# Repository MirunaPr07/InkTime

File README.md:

# InkWatch_TSC_Project

## Descriere

Proiectul meu este un smartwatch simplificat, cu focus pe consum redus și integrarea mai multor funcționalități pe un PCB mic. Am folosit un nRF52840 ca MCU principal și am conectat la el senzori, display e-paper și haptic.

Funcționalități:
- display e-paper
- BLE pentru comunicare
- accelerometru pentru mișcare
- feedback haptic
- încărcare USB-C

---

## Schema Bloc

```mermaid
graph TD

    USB["USB-C (J4)"] --> CHARGER["BQ25180 Charger"]
    CHARGER --> REG["RT6160 3.3V"]
    REG --> MCU["nRF52840 MCU + BLE"]

    BAT["LiPo Battery"] --> CHARGER
    BAT --> FUEL["MAX17048 Fuel Gauge"]
    FUEL --> MCU

    MCU -->|SPI| EPD["EPD Display (J1)"]
    MCU -->|I2C| IMU["BMA421 IMU"]
    MCU -->|I2C| HAPTIC["DRV2605 Haptic"]

    MCU --> BTN1["SW_UP"]
    MCU --> BTN2["SW_DN"]
    MCU --> BTN3["SW_ENT"]

    MCU --> ANT["2.4GHz Antenna"]

    MCU --> DEBUG["TC2030 SWD"]
```

## Bill of Materials

| Ref | Component | Package | Funcție | LCSC | Datasheet |
|-----|----------|--------|--------|------|----------|
| U1 | nRF52840-QIAA | QFN73 | MCU + BLE | [C190794](https://jlcpcb.com/partdetail/C190794) | https://infocenter.nordicsemi.com |
| IC1 | BQ25180YBGR | DSBGA-8 | Charger LiPo | [C3682423](https://jlcpcb.com/partdetail/C3682423) | https://www.ti.com |
| IC9 | RT6160AWSC | WLCSP-15 | Regulator 3.3V | [C7065276](https://jlcpcb.com/partdetail/C7065276) | https://www.richtek.com |
| U3 | MAX17048G+T10 | DFN | Fuel gauge | [C2682616](https://jlcpcb.com/partdetail/C2682616) | https://www.analog.com |
| IC3 | BMA421 | LGA | IMU | [C5242966](https://jlcpcb.com/partdetail/C5242966) | https://www.bosch-sensortec.com |
| IC2 | DRV2605L | VSSOP | Haptic driver | [C527464](https://jlcpcb.com/partdetail/C527464) | https://www.ti.com |
| D3 | USBLC6 | SOT-23-6 | ESD USB | [C2687116](https://jlcpcb.com/partdetail/C2687116) | https://www.st.com |
| J4 | USB-C | SMD | Conector alimentare | [C165948](https://jlcpcb.com/partdetail/C165948) | - |
| J1 | FPC 24 pini | SMD | Conector display | [C393234](https://jlcpcb.com/partdetail/C393234) | - |
| J2 | TC2030 | PTH | Debug SWD | - | - |
| ANT1 | 2450AT18B100E | SMD | Antenă BLE | - | https://www.johansontechnology.com |

---

## Funcționalitate Hardware

### Power

USB-C (5V) -> BQ25180 -> RT6160 -> 3.3V -> sistem

- BQ25180 face charging + power path
- RT6160 generează 3.3V stabil
- MAX17048 citește nivelul bateriei

---

### MCU - nRF52840

Este componenta principală:
- BLE integrat
- controlează toate perifericele

---

### Display E-Paper

Conectat prin SPI:
- SCK - P0.02
- MOSI - P0.03
- CS - P0.05
- DC - P0.15
- RST - P0.16
- BUSY - P0.17

---

### IMU - BMA421

- I2C (SDA P0.06 / SCL P0.07)
- interrupt pe P0.08 și P1.08

---

### Haptic – DRV2605

- I2C
- enable pe P0.12

---

### USB

- USB-C pentru alimentare
- protecție ESD (USBLC6)

---

## Pini nRF52840

| Pin | Semnal | Funcție |
|-----|--------|--------|
| P0.02 | SCK | SPI |
| P0.03 | MOSI | SPI |
| P0.05 | CS | Display |
| P0.06 | SDA | I2C |
| P0.07 | SCL | I2C |
| P0.08 | INT1 | IMU |
| P0.12 | HAPTIC_EN | Haptic |
| P0.13 | SW_UP | Buton |
| P0.14 | SW_DN | Buton |
| P0.15 | DC | Display |
| P0.16 | RST | Display |
| P0.17 | BUSY | Display |
| P1.00 | SW_ENT | Buton |
| P1.01 | EPD_PWR | Power gate |
| P1.08 | INT2 | IMU |
| P0.24 | SWDCLK | Debug |
| P0.25 | SWDIO | Debug |

---

## PCB Design

- 2 layere (Top + Bottom)
- GND polygon pour pe ambele
- trasee:
  - power: 0.3mm
  - semnal: 0.15mm

### Decizii:
- antena la margine cu keepout
- decuplare lângă IC-uri
- rutare manuală pentru trasee critice

---

## Observații

- rutare destul de densă în zona MCU
- unele trasee mai subțiri în zona BGA
- câteva GND trase manual

---

## Concluzie

Proiectul este complet funcțional din punct de vedere hardware și include toate modulele necesare pentru un smartwatch simplu.

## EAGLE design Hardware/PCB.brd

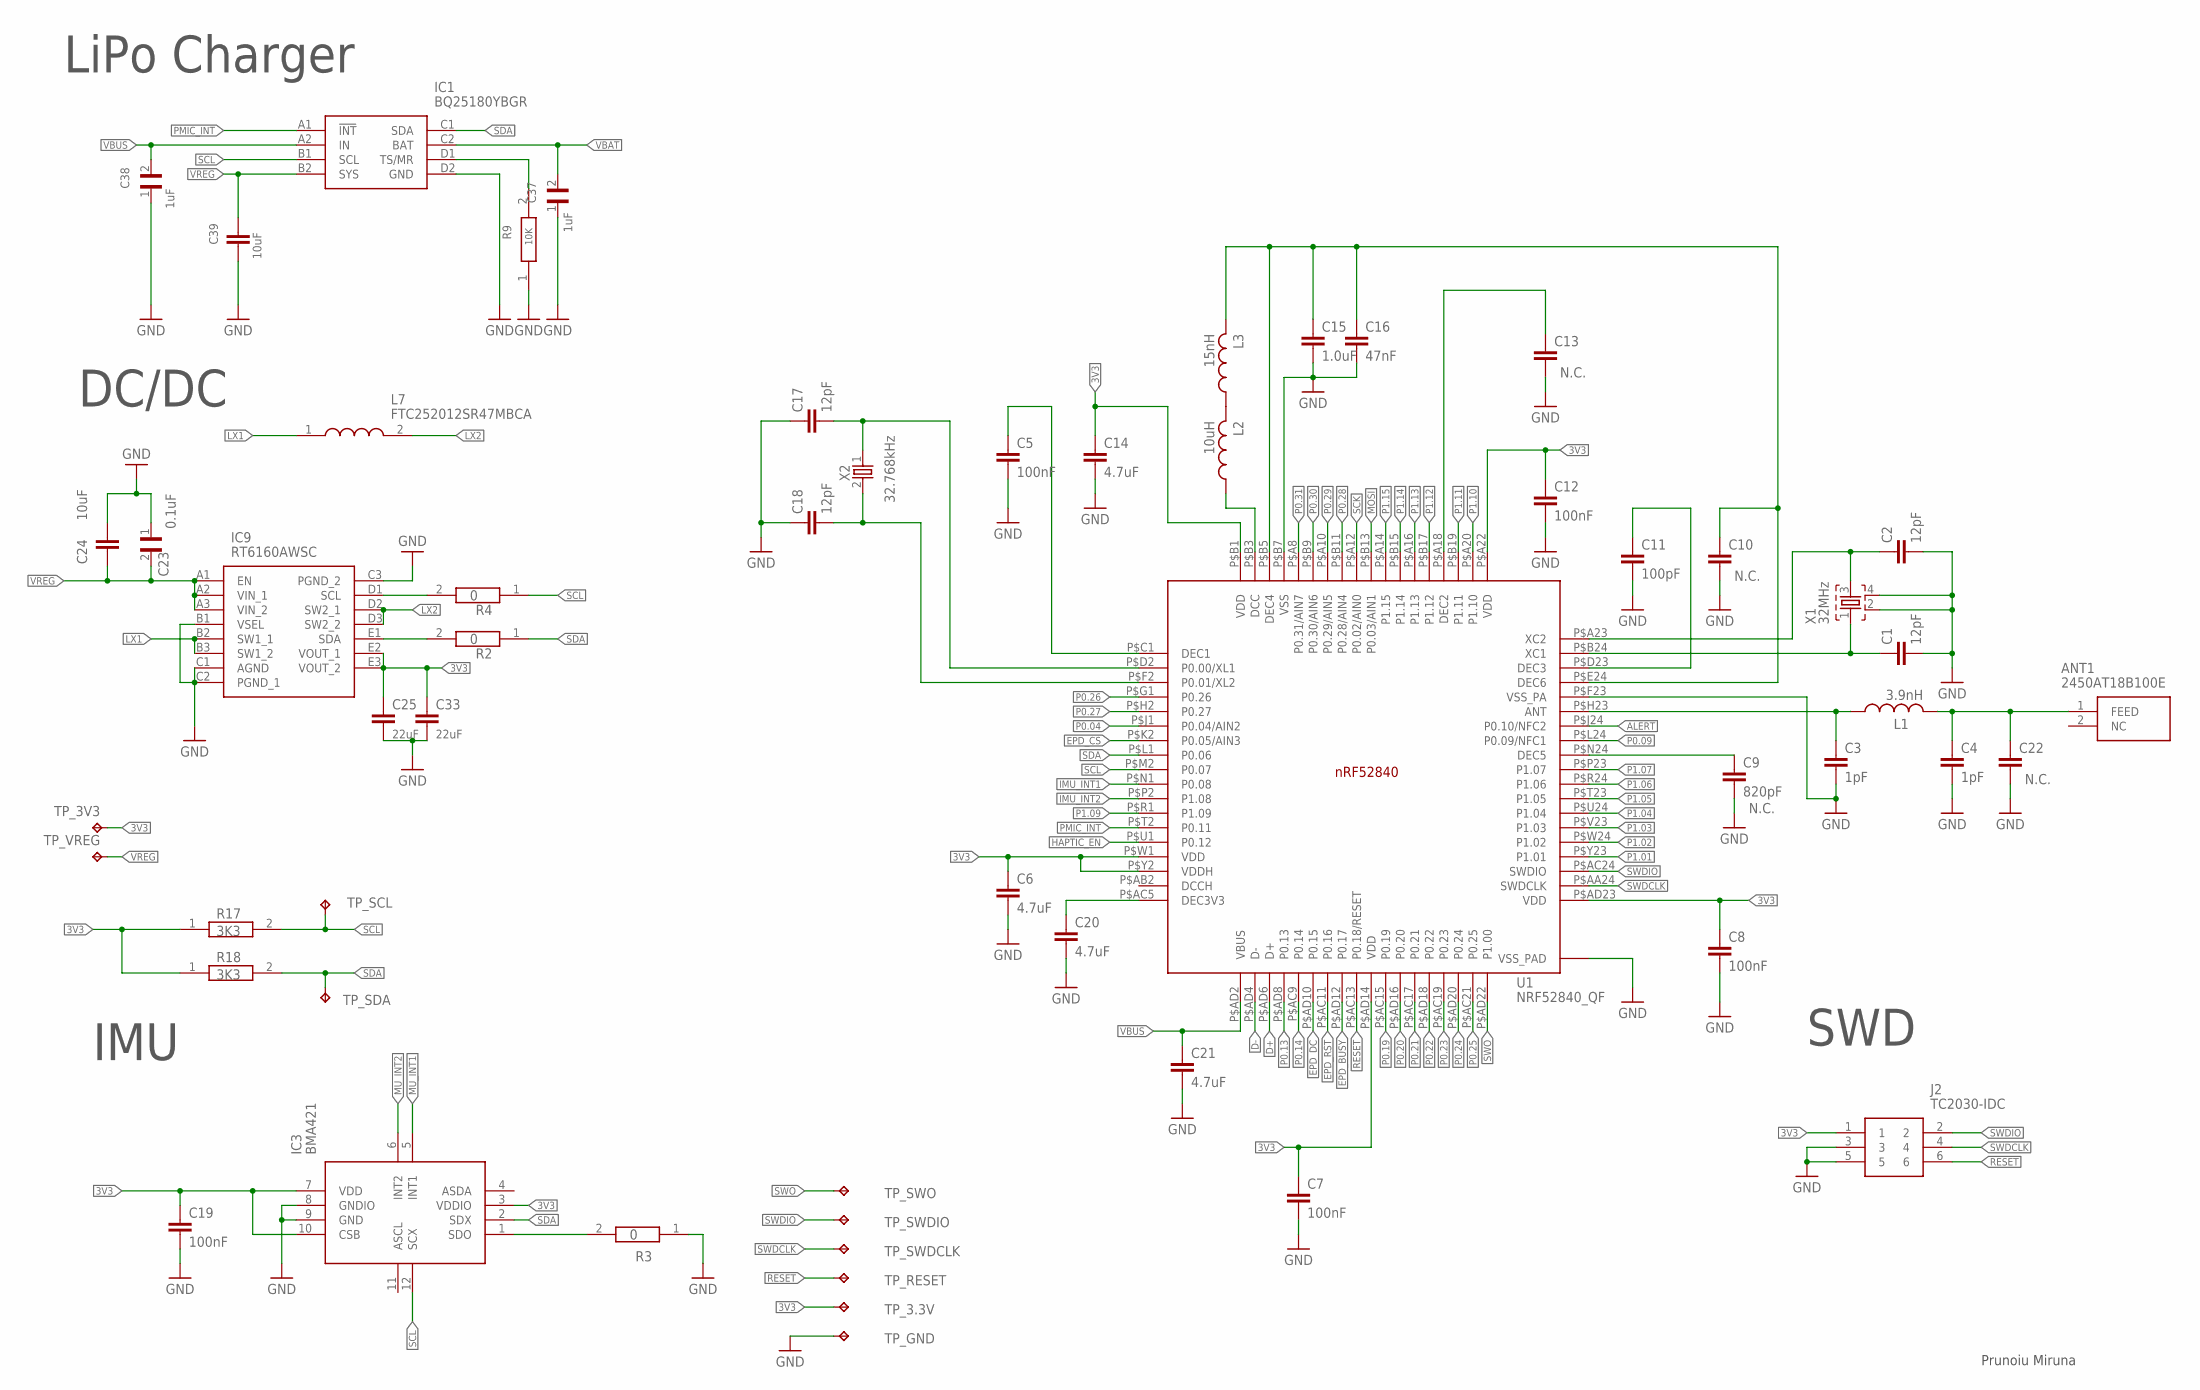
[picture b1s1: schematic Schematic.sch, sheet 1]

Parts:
ANT1: 2450AT18B100E; 2450AT18B100E_ANTC3216X140N
C1, C2, C17, C18: 12pF; NORDIC_NRF_3_RESC0201_L
C3, C4: 1pF; NORDIC_NRF_3_RESC0201_L
C5, C7, C8, C12, C19: 100nF; NORDIC_NRF_3_RESC0201_L
C6, C14, C20, C21: 4.7uF; NORDIC_NRF_3_RESC0201_L
C9: 820pF; NORDIC_NRF_3_RESC0201_L
C10, C13, C22: NORDIC_NRF_3_CAPACITOR_0201_L; NORDIC_NRF_3_RESC0201_L
C11: 100pF; NORDIC_NRF_3_RESC0201_L
C15: 1.0uF; NORDIC_NRF_3_RESC0201_L
C16: 47nF; NORDIC_NRF_3_RESC0201_L
C23: 0.1uF; GRM011R60J152KE01L_1_0201
C24, C39: 10uF; NORDIC_NRF_3_RESC0201_L
C25, C33: 22uF; NORDIC_NRF_3_RESC0201_L
C37, C38: 1uF; GRM011R60J152KE01L_1_0201
IC1: BQ25180YBGR; BQ25180YBGR_BGA8C40P2X4_100X155X50
IC3: BMA421; BMA423_BMA423
IC9: RT6160AWSC; RT6160AWSC_BGA15C40P3X5_140X230X60
J2: TC2030-IDC; TC2030-IDC_TC2030IDC
L1: 3.9nH; NORDIC_NRF_2_RESC0402_L
L2: 10uH; NORDIC_NRF_2_RESC0402_L
L3: 15nH; NORDIC_NRF_2_RESC0402_L
L7: FTC252012SR47MBCA; MLP2016SR47MT0S1_INDC2016X100N
R2, R3, R4: 0; CPF0201D7K68C1_0201
R9: 10K; CPF0201D7K68C1_0201
R17, R18: 3K3; CPF0201D7K68C1_0201
TP_3.3V, TP_3V3: HECTOR_WATCH_1_TPTP20R; HECTOR_WATCH_1_TP20R
TP_GND: HECTOR_WATCH_1_TPTP20R; HECTOR_WATCH_1_TP20R
TP_RESET: HECTOR_WATCH_1_TPTP20R; HECTOR_WATCH_1_TP20R
TP_SCL: HECTOR_WATCH_1_TPTP20R; HECTOR_WATCH_1_TP20R
TP_SDA: HECTOR_WATCH_1_TPTP20R; HECTOR_WATCH_1_TP20R
TP_SWDCLK: HECTOR_WATCH_1_TPTP20R; HECTOR_WATCH_1_TP20R
TP_SWDIO: HECTOR_WATCH_1_TPTP20R; HECTOR_WATCH_1_TP20R
TP_SWO: HECTOR_WATCH_1_TPTP20R; HECTOR_WATCH_1_TP20R
TP_VREG: HECTOR_WATCH_1_TPTP20R; HECTOR_WATCH_1_TP20R
U1: NRF52840_QF; NORDIC_NRF_4_AQFN50P700X700X85_HS-74N
X1: 32MHz; NORDIC_NRF_BT-XTAL_2016_N
X2: 32.768kHz; NORDIC_NRF_1_XTAL_3215_N

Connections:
3V3: C6.1, C7.1, C8.1, C12.1, C14.1, C19.1, C25.1, C33.1, IC3.3 (VDDIO), IC3.7 (VDD), IC3.10 (CSB), IC9.E2 (VOUT_1), IC9.E3 (VOUT_2), J2.1, R17.1, R18.1, TP_3.3V.TP, TP_3V3.TP, U1.P$A22 (VDD), U1.P$AD14 (VDD), U1.P$AD23 (VDD), U1.P$B1 (VDD), U1.P$W1 (VDD), U1.P$Y2 (VDDH); also elsewhere on the board
ALERT: U1.P$J24 (P0.10/NFC2); also elsewhere on the board
D+: U1.P$AD6 (D+); also elsewhere on the board
D-: U1.P$AD4 (D-); also elsewhere on the board
DEC1: C5.1, U1.P$C1 (DEC1)
DEC3: C11.1, U1.P$D23 (DEC3)
DEC4_6: C10.1, C15.1, C16.1, L3.2, U1.P$B5 (DEC4), U1.P$E24 (DEC6)
EPD_BUSY: U1.P$AD12 (P0.17); also elsewhere on the board
EPD_CS: U1.P$K2 (P0.05/AIN3); also elsewhere on the board
EPD_DC: U1.P$AD10 (P0.15); also elsewhere on the board
EPD_RST: U1.P$AC11 (P0.16); also elsewhere on the board
GND: C1.2, C2.2, C3.2, C4.2, C5.2, C6.2, C7.2, C8.2, C9.2, C10.2, C11.2, C12.2, C13.2, C14.2, C15.2, C16.2, C17.1, C18.1, C19.2, C20.2, C21.2, C22.2, C23.1, C24.1, C25.2, C33.2, C37.1, C38.1, C39.2, IC1.D2 (GND), IC3.8 (GNDIO), IC3.9 (GND), IC9.B1 (VSEL), IC9.C1 (AGND), IC9.C2 (PGND_1), IC9.C3 (PGND_2), J2.3, J2.5, R3.1, R9.1, TP_GND.TP, U1.P$74 (VSS_PAD), U1.P$75 (VSS_PAD), U1.P$76 (VSS_PAD), U1.P$77 (VSS_PAD), U1.P$78 (VSS_PAD), U1.P$79 (VSS_PAD), U1.P$80 (VSS_PAD), U1.P$81 (VSS_PAD), U1.P$82 (VSS_PAD), U1.P$83 (VSS_PAD), U1.P$84 (VSS_PAD), U1.P$85 (VSS_PAD), U1.P$86 (VSS_PAD), U1.P$87 (VSS_PAD), U1.P$88 (VSS_PAD), U1.P$89 (VSS_PAD), U1.P$90 (VSS_PAD), U1.P$B7 (VSS), U1.P$F23 (VSS_PA), X1.2, X1.4; also elsewhere on the board
HAPTIC_EN: U1.P$U1 (P0.12); also elsewhere on the board
IMU_INT1: U1.P$N1 (P0.08)
IMU_INT2: U1.P$P2 (P1.08)
LX1: IC9.B2 (SW1_1), IC9.B3 (SW1_2), L7.1
LX2: IC9.D2 (SW2_1), IC9.D3 (SW2_2), L7.2
MOSI: U1.P$B13 (P0.03/AIN1); also elsewhere on the board
MU_INT1: IC3.5 (INT1)
MU_INT2: IC3.6 (INT2)
unnamed: IC3.1 (SDO), R3.2
unnamed: IC9.E1 (SDA), R2.2
unnamed: IC9.D1 (SCL), R4.2
unnamed: C9.1, U1.P$N24 (DEC5)
unnamed: IC1.D1 (TS/MR), R9.2
unnamed: C13.1, U1.P$A18 (DEC2)
unnamed: C3.1, L1.1, U1.P$H23 (ANT)
unnamed: C1.1, U1.P$B24 (XC1), X1.1
unnamed: C2.1, U1.P$A23 (XC2), X1.3
unnamed: L2.2, L3.1
unnamed: L2.1, U1.P$B3 (DCC)
unnamed: C20.1, U1.P$AC5 (DEC3V3)
P0.00/XL1: C17.2, U1.P$D2 (P0.00/XL1), X2.1
P0.01/XL2: C18.2, U1.P$F2 (P0.01/XL2), X2.2
P0.04: U1.P$J1 (P0.04/AIN2)
P0.09: U1.P$L24 (P0.09/NFC1)
P0.13: U1.P$AD8 (P0.13); also elsewhere on the board
P0.14: U1.P$AC9 (P0.14); also elsewhere on the board
P0.19: U1.P$AC15 (P0.19)
P0.20: U1.P$AD16 (P0.20)
P0.21: U1.P$AC17 (P0.21)
P0.22: U1.P$AD18 (P0.22)
P0.23: U1.P$AC19 (P0.23)
P0.24: U1.P$AD20 (P0.24)
P0.25: U1.P$AC21 (P0.25)
P0.26: U1.P$G1 (P0.26)
P0.27: U1.P$H2 (P0.27)
P0.28: U1.P$B11 (P0.28/AIN4)
P0.29: U1.P$A10 (P0.29/AIN5)
P0.30: U1.P$B9 (P0.30/AIN6)
P0.31: U1.P$A8 (P0.31/AIN7)
P1.01: U1.P$Y23 (P1.01); also elsewhere on the board
P1.02: U1.P$W24 (P1.02); also elsewhere on the board
P1.03: U1.P$V23 (P1.03)
P1.04: U1.P$U24 (P1.04)
P1.05: U1.P$T23 (P1.05)
P1.06: U1.P$R24 (P1.06)
P1.07: U1.P$P23 (P1.07)
P1.09: U1.P$R1 (P1.09)
P1.10: U1.P$A20 (P1.10)
P1.11: U1.P$B19 (P1.11)
P1.12: U1.P$B17 (P1.12)
P1.13: U1.P$A16 (P1.13)
P1.14: U1.P$B15 (P1.14)
P1.15: U1.P$A14 (P1.15)
PMIC_INT: IC1.A1 (!INT), U1.P$T2 (P0.11)
RESET: J2.6, TP_RESET.TP, U1.P$AC13 (P0.18/RESET)
RF: ANT1.1 (FEED), C4.1, C22.1, L1.2
SCK: U1.P$A12 (P0.02/AIN0); also elsewhere on the board
SCL: IC1.B1 (SCL), IC3.12 (SCX), R4.1, R17.2, TP_SCL.TP, U1.P$M2 (P0.07); also elsewhere on the board
SDA: IC1.C1 (SDA), IC3.2 (SDX), R2.1, R18.2, TP_SDA.TP, U1.P$L1 (P0.06); also elsewhere on the board
SWDCLK: J2.4, TP_SWDCLK.TP, U1.P$AA24 (SWDCLK)
SWDIO: J2.2, TP_SWDIO.TP, U1.P$AC24 (SWDIO)
SWO: TP_SWO.TP, U1.P$AD22 (P1.00)
VBAT: C37.2, IC1.C2 (BAT); also elsewhere on the board
VBUS: C21.1, C38.2, IC1.A2 (IN), U1.P$AD2 (VBUS); also elsewhere on the board
VREG: C23.2, C24.2, C39.1, IC1.B2 (SYS), IC9.A1 (EN), IC9.A2 (VIN_1), IC9.A3 (VIN_2), TP_VREG.TP

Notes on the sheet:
IMU
LiPo Charger
DC/DC
SWD
Prunoiu Miruna

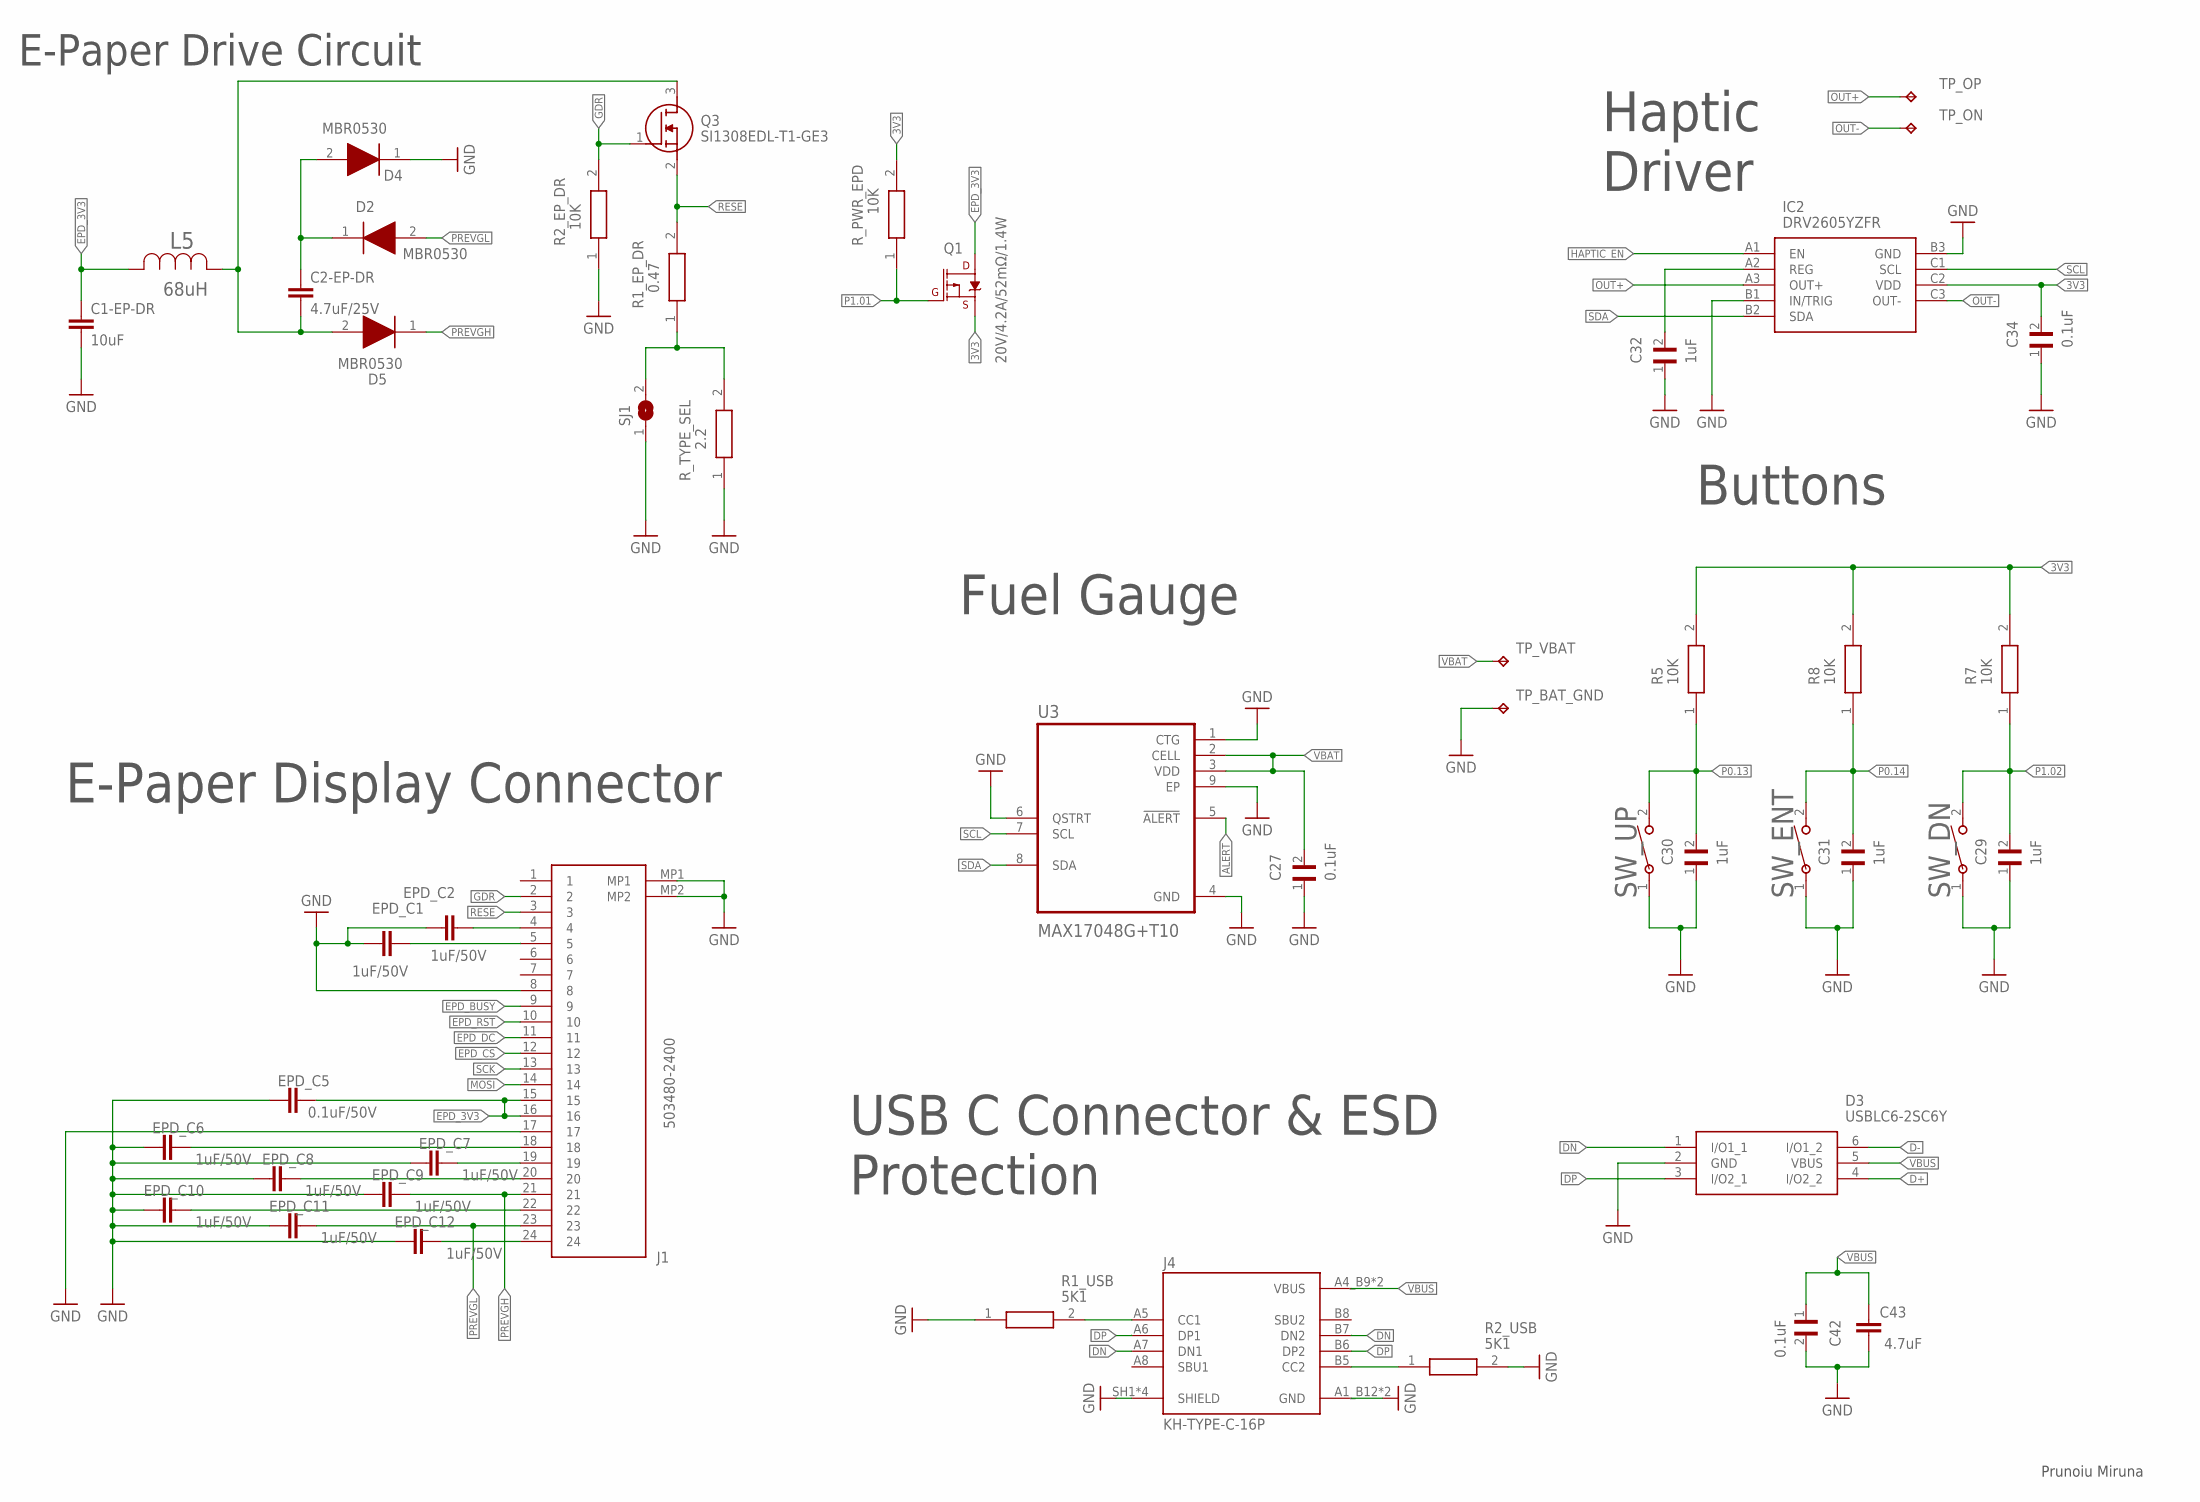
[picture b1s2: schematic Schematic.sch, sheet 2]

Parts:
C1-EP-DR: 10uF; NORDIC_NRF_3_RESC0201_L
C2-EP-DR: 4.7uF/25V; NORDIC_NRF_3_RESC0201_L
C27, C34, C42: 0.1uF; GRM011R60J152KE01L_2_CAPC0201X13N
C29, C30, C31, C32: 1uF; GRM011R60J152KE01L_2_CAPC0201X13N
C43: 4.7uF; NORDIC_NRF_3_RESC0201_L
D2, D4, D5: MBR0530; ESP32_C6_LIBRARY_5_SOD3716X135N
D3: USBLC6-2SC6Y; ESP32_C6_LIBRARY_3_SOT95P280X145-6N
EPD_C1, EPD_C2, EPD_C6, EPD_C7, EPD_C8, EPD_C9, EPD_C10, EPD_C11, EPD_C12: 1uF/50V; NORDIC_NRF_3_RESC0201_L
EPD_C5: 0.1uF/50V; NORDIC_NRF_3_RESC0201_L
IC2: DRV2605YZFR; DRV2605YZFR_BGA9C50P3X3_144X144X62
J1: 503480-2400; 503480-2400_5034802400
J4: KH-TYPE-C-16P; KH-TYPE-C-16P_KINGHELM_KH-TYPE-C-16P
L5: 68uH; ESP32_C6_LIBRARY_2_IND_4828-WE-TPC_WRE
Q1: 20V/4.2A/52mΩ/1.4W; ESP32_C6_LIBRARY_4_ESP32_C6_LIBRARY_4_ESP32_C6_LIBRARY_4_ES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
Q3: SI1308EDL-T1-GE3; ESP32_C6_LIBRARY_6_SOT65P210X110-3N
R1_EP_DR: 0.47; CPF0201D7K68C1_0201
R1_USB, R2_USB: 5K1; CPF0201D7K68C1_0201
R2_EP_DR, R5, R7, R8: 10K; CPF0201D7K68C1_0201
R_PWR_EPD: 10K; CPF0201D7K68C1_0201
R_TYPE_SEL: 2.2; CPF0201D7K68C1_0201
SJ1: ESP32_C6_LIBRARY_7_JUMPER_SJ
SW_DN: 2025-10-22_07-23-44_LIBRARY_EVP-AKE31ASW_EVP-AKE3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; 2025-10-22_07-23-44_LIBRARY_SW_EVP-AKE31A_PAN
SW_ENT: 2025-10-22_07-23-44_LIBRARY_EVP-AKE31ASW_EVP-AKE3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; 2025-10-22_07-23-44_LIBRARY_SW_EVP-AKE31A_PAN
SW_UP: 2025-10-22_07-23-44_LIBRARY_EVP-AKE31ASW_EVP-AKE3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; 2025-10-22_07-23-44_LIBRARY_SW_EVP-AKE31A_PAN
TP_BAT_GND: HECTOR_WATCH_1_TPTP20R; HECTOR_WATCH_1_TP20R
TP_ON: HECTOR_WATCH_1_TPTP20R; HECTOR_WATCH_1_TP20R
TP_OP: HECTOR_WATCH_1_TPTP20R; HECTOR_WATCH_1_TP20R
TP_VBAT: HECTOR_WATCH_1_TPTP20R; HECTOR_WATCH_1_TP20R
U3: MAX17048G+T10; ESP32_C6_LIBRARY_SON50P200X200X80-9N

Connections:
3V3: C34.2, IC2.C2 (VDD), Q1.2 (S), R5.2, R7.2, R8.2, R_PWR_EPD.2; also elsewhere on the board
ALERT: U3.5 (!ALERT); also elsewhere on the board
D+: D3.4 (I/O2_2); also elsewhere on the board
D-: D3.6 (I/O1_2); also elsewhere on the board
DN: D3.1 (I/O1_1), J4.A7 (DN1), J4.B7 (DN2)
DP: D3.3 (I/O2_1), J4.A6 (DP1), J4.B6 (DP2)
EPD_3V3: C1-EP-DR.1, EPD_C5.2, J1.15, J1.16, L5.2, Q1.3 (D)
EPD_BUSY: J1.9; also elsewhere on the board
EPD_CS: J1.12; also elsewhere on the board
EPD_DC: J1.11; also elsewhere on the board
EPD_RST: J1.10; also elsewhere on the board
GDR: J1.2, Q3.1 (G), R2_EP_DR.2
GND: C1-EP-DR.2, C27.1, C29.1, C30.1, C31.1, C32.1, C34.1, C42.2, C43.1, D3.2 (GND), D4.1 (K), EPD_C1.1, EPD_C2.1, EPD_C5.1, EPD_C6.1, EPD_C7.1, EPD_C8.1, EPD_C9.1, EPD_C10.1, EPD_C11.1, EPD_C12.1, IC2.B1 (IN/TRIG), IC2.B3 (GND), J1.8, J1.17, J1.MP1, J1.MP2, J4.A1_B12 (GND), J4.A12_B1 (GND), J4.SH1 (SHIELD), J4.SH2 (SHIELD), J4.SH3 (SHIELD), J4.SH4 (SHIELD), R1_USB.1, R2_EP_DR.1, R2_USB.2, R_TYPE_SEL.1, SJ1.1, SW_DN.1, SW_ENT.1, SW_UP.1, TP_BAT_GND.TP, U3.1 (CTG), U3.4 (GND), U3.6 (QSTRT), U3.9 (EP); also elsewhere on the board
HAPTIC_EN: IC2.A1 (EN); also elsewhere on the board
MOSI: J1.14; also elsewhere on the board
unnamed: C32.2, IC2.A2 (REG)
unnamed: C2-EP-DR.2, D5.2 (A), L5.1, Q3.3 (D)
unnamed: C2-EP-DR.1, D2.1 (K), D4.2 (A)
unnamed: J4.A5 (CC1), R1_USB.2
unnamed: J4.B5 (CC2), R2_USB.1
unnamed: EPD_C2.2, J1.4
unnamed: EPD_C1.2, J1.5
unnamed: R1_EP_DR.1, R_TYPE_SEL.2, SJ1.2
unnamed: EPD_C6.2, J1.18
unnamed: EPD_C7.2, J1.19
unnamed: EPD_C8.2, J1.20
unnamed: EPD_C10.2, J1.22
unnamed: EPD_C12.2, J1.24
OUT+: IC2.A3 (OUT+), TP_OP.TP
OUT-: IC2.C3 (OUT-), TP_ON.TP
P0.13: C30.2, R5.1, SW_UP.2; also elsewhere on the board
P0.14: C31.2, R8.1, SW_ENT.2; also elsewhere on the board
P1.01: Q1.1 (G), R_PWR_EPD.1; also elsewhere on the board
P1.02: C29.2, R7.1, SW_DN.2; also elsewhere on the board
PREVGH: D5.1 (K), EPD_C9.2, J1.21
PREVGL: D2.2 (A), EPD_C11.2, J1.23
RESE: J1.3, Q3.2 (S), R1_EP_DR.2
SCK: J1.13; also elsewhere on the board
SCL: IC2.C1 (SCL), U3.7 (SCL); also elsewhere on the board
SDA: IC2.B2 (SDA), U3.8 (SDA); also elsewhere on the board
VBAT: C27.2, TP_VBAT.TP, U3.2 (CELL), U3.3 (VDD); also elsewhere on the board
VBUS: C42.1, C43.2, D3.5 (VBUS), J4.A4_B9 (VBUS), J4.A9_B4 (VBUS); also elsewhere on the board

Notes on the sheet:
E-Paper Drive Circuit
Haptic Driver
USB C Connector & ESD Protection
Buttons
Fuel Gauge
E-Paper Display Connector
Prunoiu Miruna

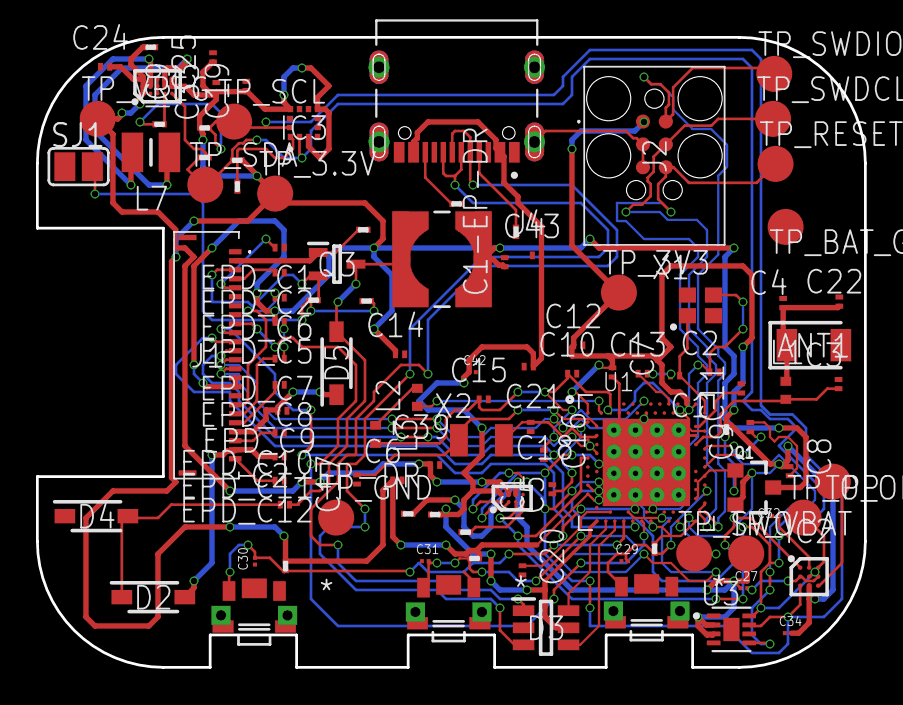
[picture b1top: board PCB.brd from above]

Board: 2 copper layers, 46.0 x 35.0 mm, 105 parts (0 on the bottom side), 68 nets.

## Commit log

2026-04-22 Final project with complete 3D model and exploded view
2026-04-22 Final commit

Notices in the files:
parts and their libraries:
COPYRIGHT: Copyright (C) 2024 Ultra Librarian. All rights reserved.
COPYRIGHT: Copyright (C) 2025 Ultra Librarian. All rights reserved.
